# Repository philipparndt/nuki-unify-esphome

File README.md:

# nuki esphome

Open Nuki lock with a relay (Unifi Door) 

## First upload

- Run `./build.sh` to build the firmware. You can find the result in `./firmware.bin`
- Use [esphome-flasher](https://github.com/esphome/esphome-flasher/releases) to flash the image
  Note that the MAC address that will be printed in this tool is the Wifi address of the ESP32
  and not the Ethernet address.

## Update the firmware

Run `./run.sh` to do a OTA update.

## Get 1-wire sensor addresses

Set the log level to `DEBUG` in `app.yaml` and observe the output of the console.
There will be a list of sensor addresses.

https://www.youtube.com/watch?v=XvA3UMDDrAQ

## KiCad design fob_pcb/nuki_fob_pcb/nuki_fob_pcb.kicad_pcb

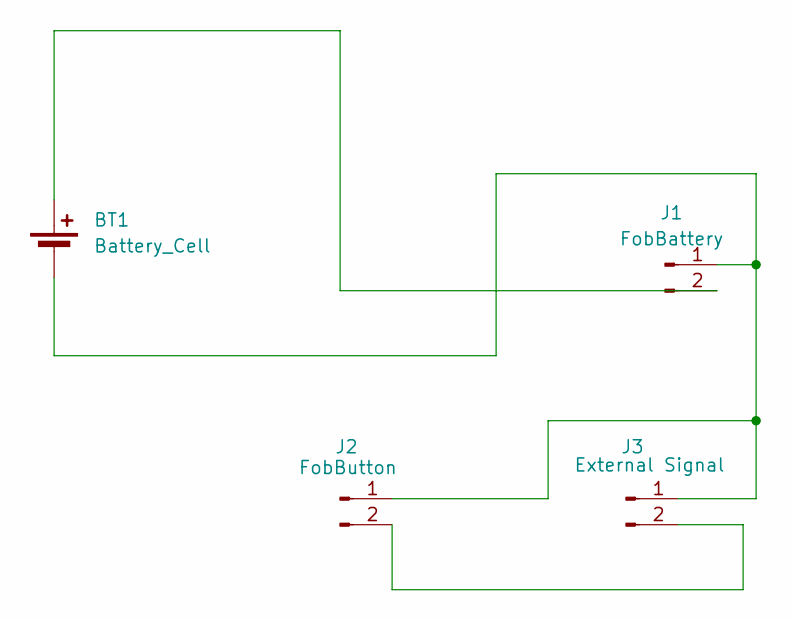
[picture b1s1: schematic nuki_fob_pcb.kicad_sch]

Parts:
BT1: Battery_Cell; BatteryHolder_Keystone_1057_1x2032
J1: FobBattery; JST_EH_B2B-EH-A_1x02_P2.50mm_Vertical
J2: FobButton; JST_EH_B2B-EH-A_1x02_P2.50mm_Vertical
J3: External Signal; JST_EH_B2B-EH-A_1x02_P2.50mm_Vertical

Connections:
unnamed: BT1.1 (+), J1.2
unnamed: BT1.2 (-), J1.1, J2.1, J3.1
unnamed: J2.2, J3.2

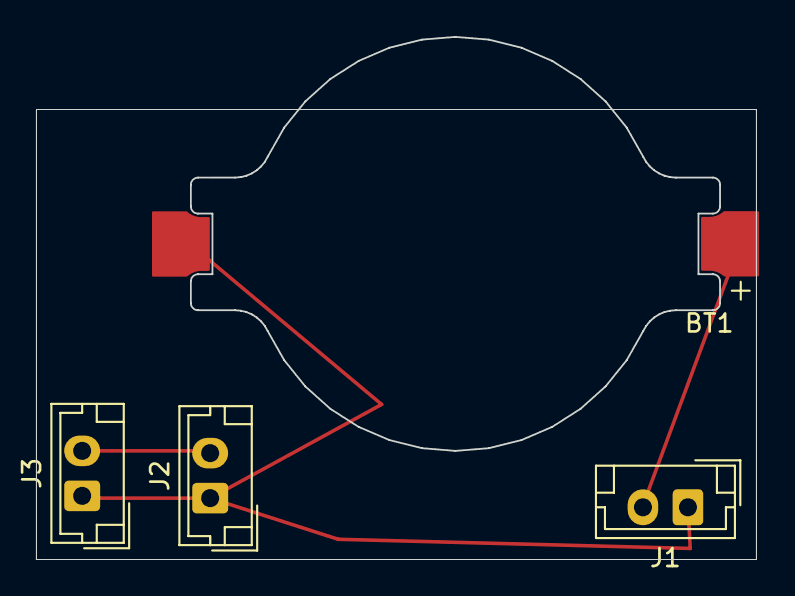
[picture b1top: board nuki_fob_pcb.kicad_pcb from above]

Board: 2 copper layers, 39.9 x 29.0 mm, 4 parts (0 on the bottom side), 3 nets.

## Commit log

2025-02-13 initial
2025-02-13 Add renovate.json
